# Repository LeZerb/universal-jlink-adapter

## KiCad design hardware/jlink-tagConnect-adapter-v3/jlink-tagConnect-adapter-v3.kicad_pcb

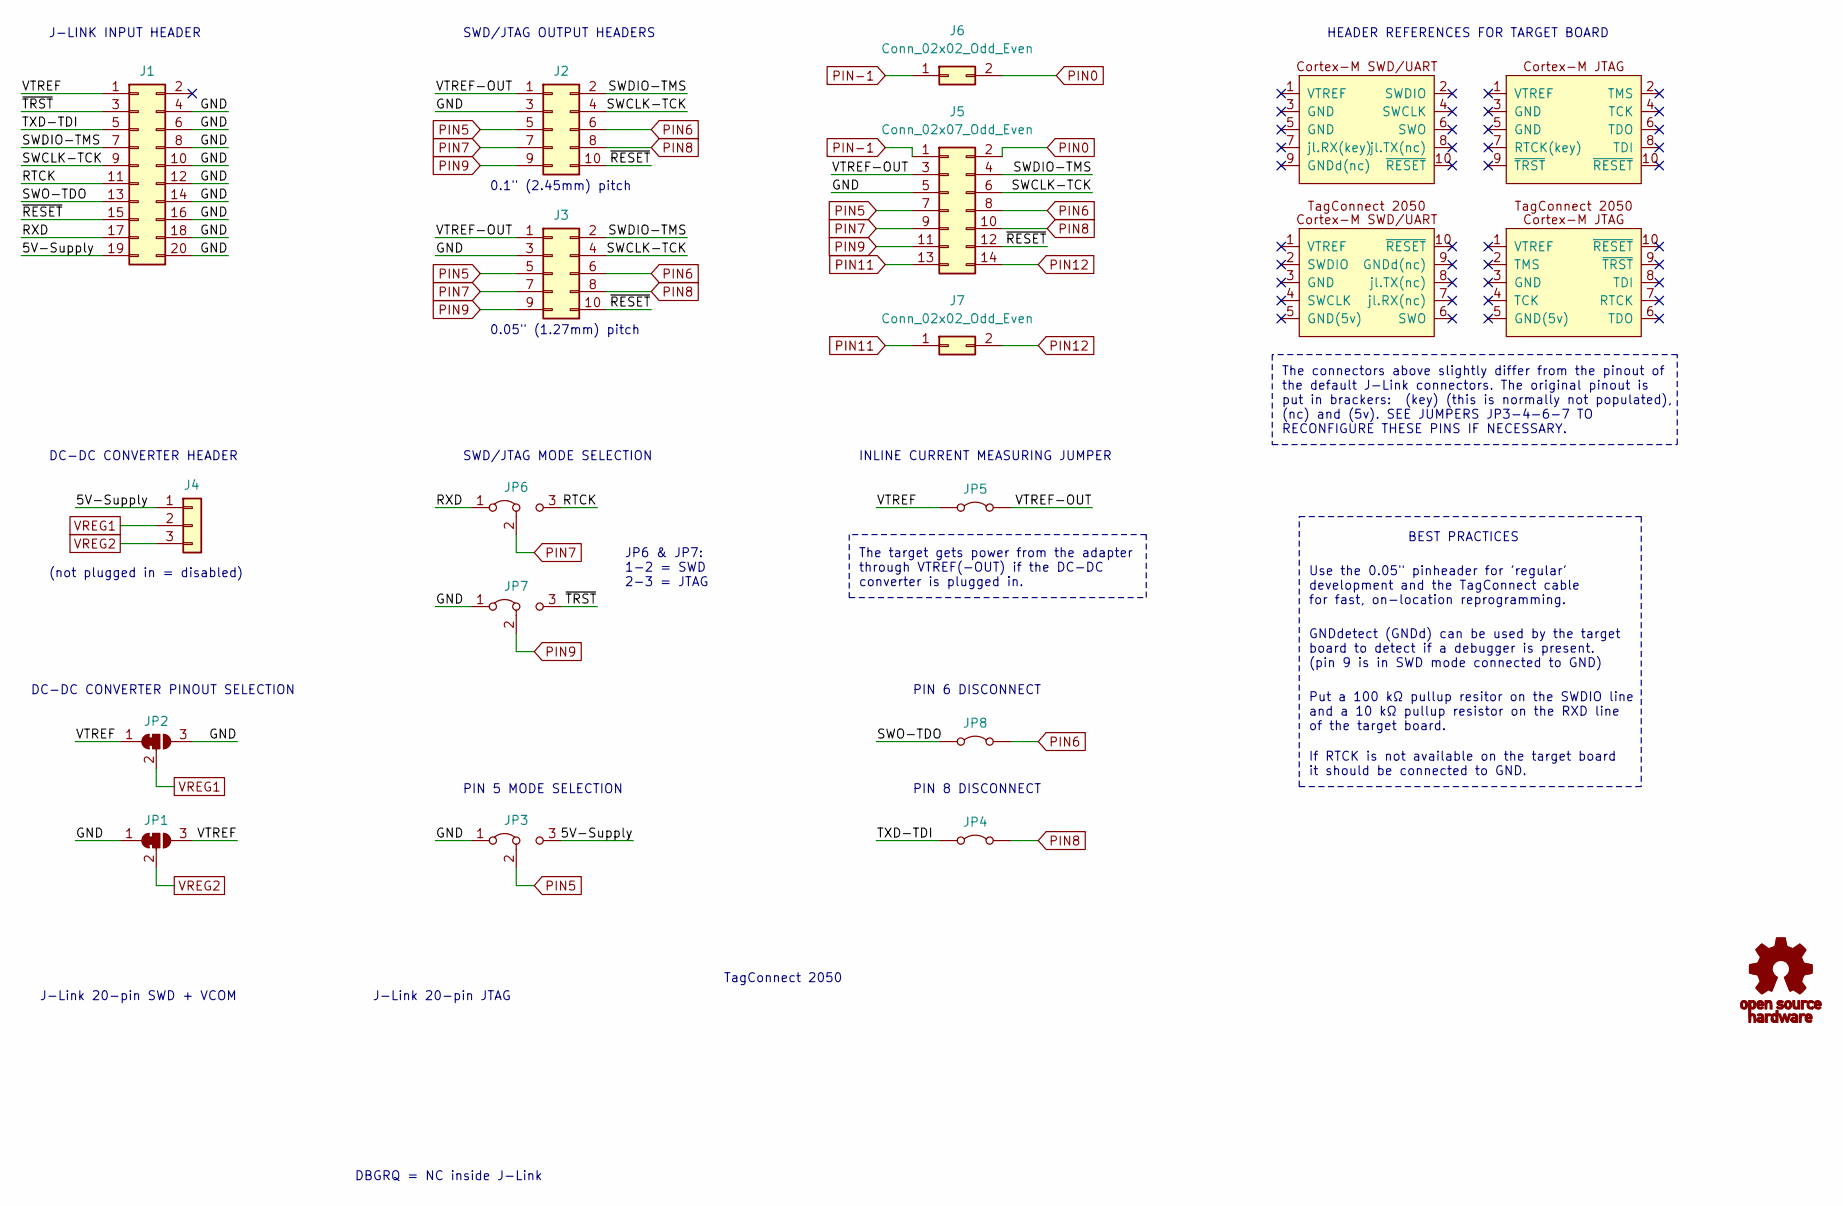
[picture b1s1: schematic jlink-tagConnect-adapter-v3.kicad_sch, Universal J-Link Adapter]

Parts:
G1: Symbol_OSHW-Logo_11.4x12mm; OSHW-Logo_5.7x6mm_SolderMask
J1: Conn_02x10_Odd_Even; PinSocket_2x10_P2.54mm_Horizontal
J2: Conn_02x05_Odd_Even; IDC-Header_2x05_P2.54mm_Vertical
J3: Conn_02x05_Odd_Even; PinHeader_2x05_P1.27mm_Vertical
J4: Conn_01x03; PinSocket_1x03_P2.54mm_Vertical
J5: Conn_02x07_Odd_Even; PinHeader_2x07_P1.27mm_Vertical
J6, J7: Conn_02x02_Odd_Even; PinHeader_2x01_P2.54mm_Vertical
JP1, JP2: SolderJumper_3_Bridged12; SolderJumper-3_P1.3mm_Bridged12_Pad1.0x1.5mm_NumberLabels
JP3, JP6, JP7: Jumper_3_Bridged12; PinHeader_1x03_P2.54mm_Vertical
JP4, JP5, JP8: Jumper_2_Bridged; PinHeader_1x02_P2.54mm_Vertical

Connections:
/5V-Supply: J1.19, J4.1, JP3.3 (B)
/GND: J1.4, J1.6, J1.8, J1.10, J1.12, J1.14, J1.16, J1.18, J1.20, J2.3, J3.3, J5.5, JP1.1 (A), JP2.3 (B), JP3.1 (A), JP7.1 (A)
/RTCK: J1.11, JP6.3 (B)
/RXD: J1.17, JP6.1 (A)
/SWCLK-TCK: J1.9, J2.4, J3.4, J5.6
/SWDIO-TMS: J1.7, J2.2, J3.2, J5.4
/SWO-TDO: J1.13, JP8.1 (A)
/TXD-TDI: J1.5, JP4.1 (A)
/VTREF: J1.1, JP1.3 (B), JP2.1 (A), JP5.1 (A)
/VTREF-OUT: J2.1, J3.1, J5.3, JP5.2 (B)
/~RESET: J1.15, J2.10, J3.10, J5.12
/~TRST: J1.3, JP7.3 (B)
PIN0: J5.2, J6.2
PIN5: J2.5, J3.5, J5.7, JP3.2 (C)
PIN6: J2.6, J3.6, J5.8, JP8.2 (B)
PIN7: J2.7, J3.7, J5.9, JP6.2 (C)
PIN8: J2.8, J3.8, J5.10, JP4.2 (B)
PIN9: J2.9, J3.9, J5.11, JP7.2 (C)
PIN11: J5.13, J7.1
PIN12: J5.14, J7.2
PIN-1: J5.1, J6.1
VREG1: J4.2, JP2.2 (C)
VREG2: J4.3, JP1.2 (C)

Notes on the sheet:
INLINE CURRENT MEASURING JUMPER
J-Link 20-pin SWD + VCOM
The target gets power from the adapter through VTREF(-OUT) if the DC-DC converter is plugged in.
HEADER REFERENCES FOR TARGET BOARD
SWD/JTAG OUTPUT HEADERS
DC-DC CONVERTER PINOUT SELECTION
Use the 0.05" pinheader for 'regular' development and the TagConnect cable for fast, on-location reprogramming.
J-Link 20-pin JTAG
PIN 8 DISCONNECT
J-LINK INPUT HEADER
DC-DC CONVERTER HEADER
TagConnect 2050
GNDdetect (GNDd) can be used by the target board to detect if a debugger is present. (pin 9 is in SWD mode connected to GND)
(not plugged in = disabled)
Put a 100 kΩ pullup resitor on the SWDIO line and a 10 kΩ pullup resistor on the RXD line of the target board.
If RTCK is not available on the target board it should be connected to GND.
The connectors above slightly differ from the pinout of the default J-Link connectors. The original pinout is put in brackers: (key) (this is normally not populated), (nc) and (5v). SEE JUMPERS JP3-4-6-7 TO RECONFIGURE THESE PINS IF NECESSARY.
PIN 6 DISCONNECT
0.05" (1.27mm) pitch
SWD/JTAG MODE SELECTION
DBGRQ = NC inside J-Link
BEST PRACTICES
JP6 & JP7: 1-2 = SWD 2-3 = JTAG
0.1" (2.45mm) pitch
PIN 5 MODE SELECTION

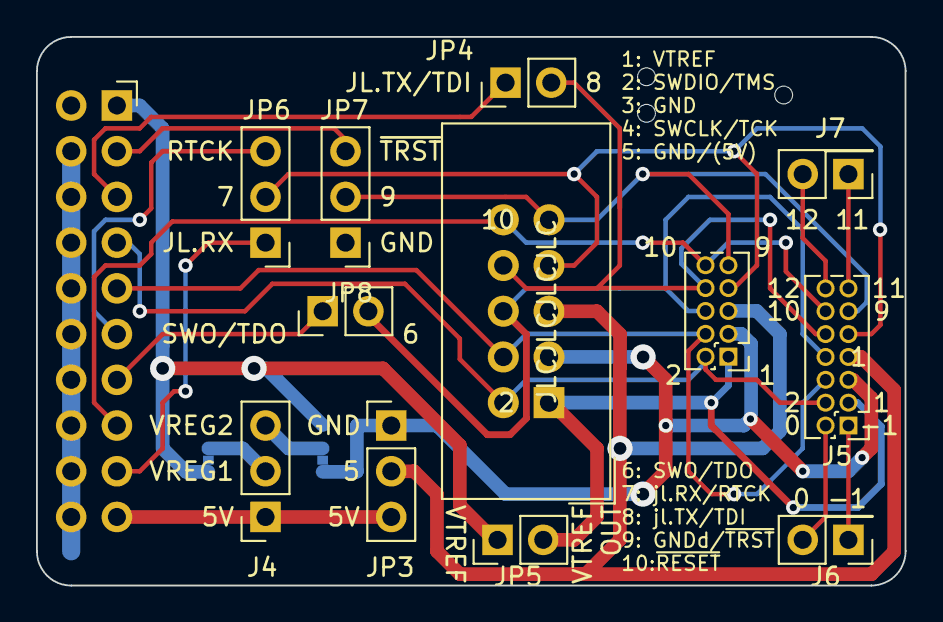
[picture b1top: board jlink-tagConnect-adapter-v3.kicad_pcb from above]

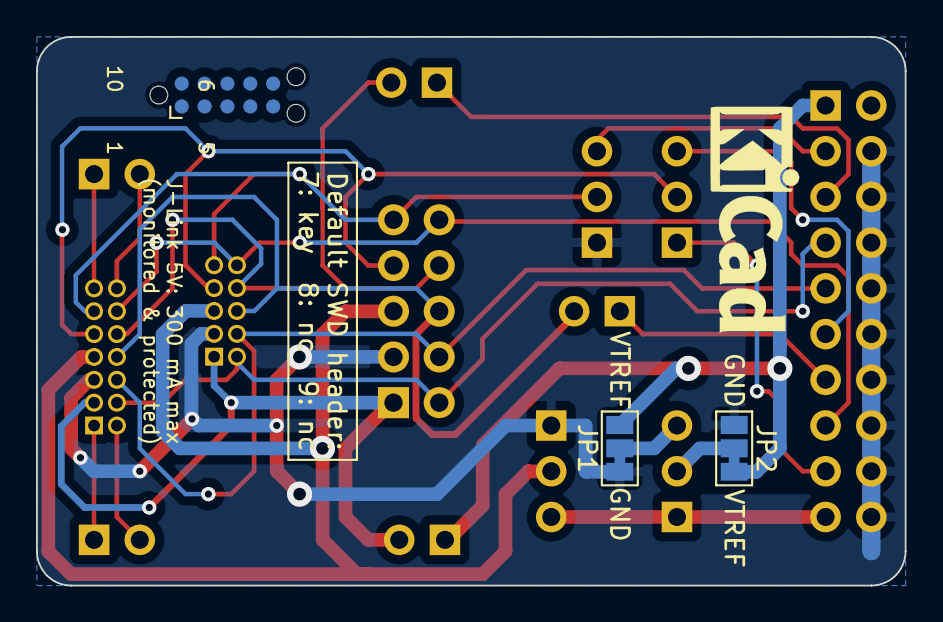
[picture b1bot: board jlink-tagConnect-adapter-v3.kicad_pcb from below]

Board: 2 copper layers, 48.3 x 30.5 mm, 15 parts (2 on the bottom side), 23 nets.

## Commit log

2024-11-15 Added 2x7 1.27mm Pinheader
    (see STM32 STDC14 debug connector which uses the outer pins for UART)
